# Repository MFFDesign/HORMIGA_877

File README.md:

# HORMIGA_877
Conjunto de procedimientos para, usar mas facilmente la placa Hormiga 877

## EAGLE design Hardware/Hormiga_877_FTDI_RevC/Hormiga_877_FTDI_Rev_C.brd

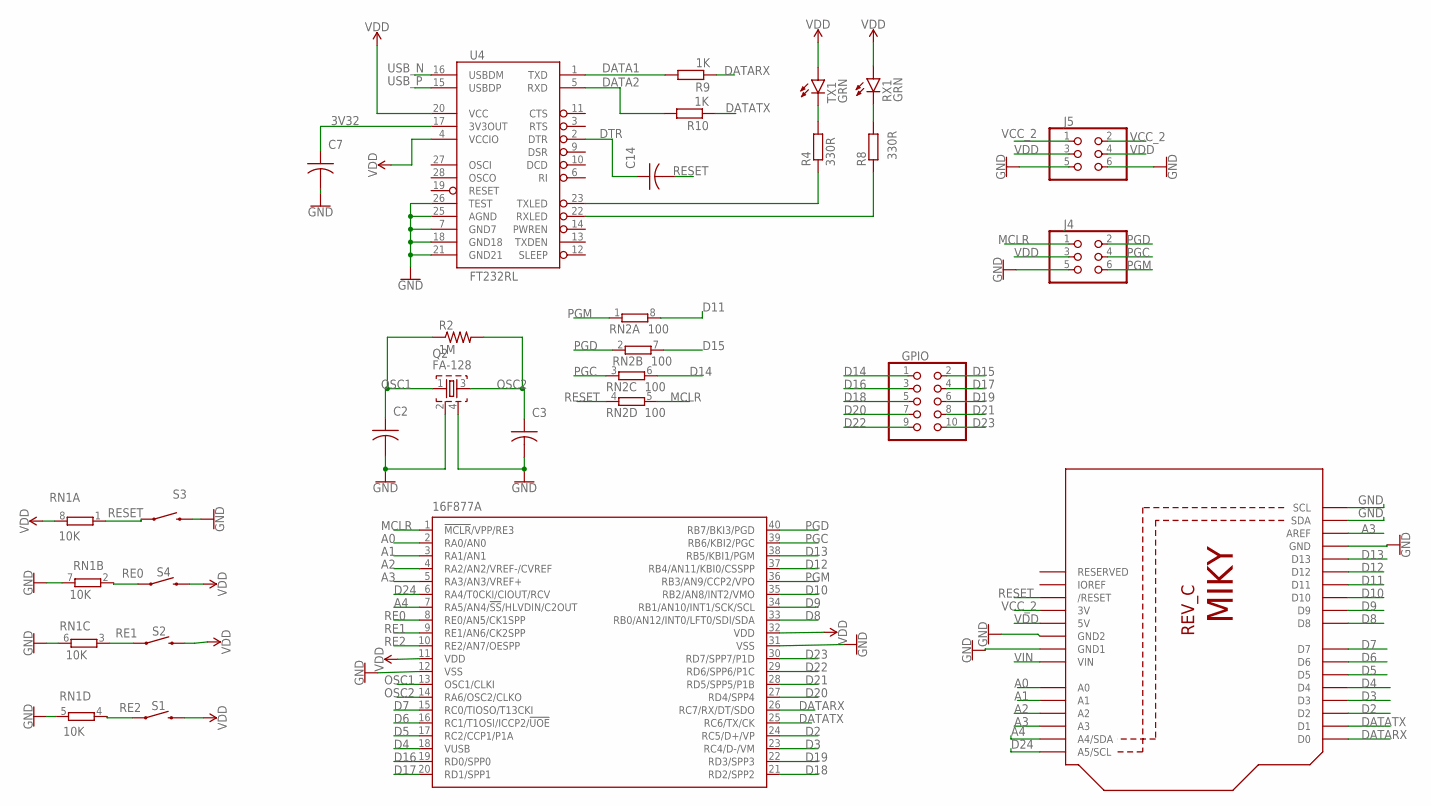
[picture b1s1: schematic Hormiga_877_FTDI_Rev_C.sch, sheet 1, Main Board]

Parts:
16F877A: PIC18F4550_40; DIL40
C2, C3: 15pF; C0603; MPN CC0402JRNPO9BN150
C7, C14: 0.1uF; C0603; MPN C0603C103J1RACTU
GPIO: PINHD-2X5; 2X05
J4: ICSP; 2X03
J5: POWER; 2X03
Q2: FA-128
R2: 1M; R0603
R4, R8: 330R; R0805; MPN ERJ-6GEYJ331V
R9, R10: 1K; R0805; MPN EXB-V8V103JV
RN1: 10K; 0603-ARC; MPN EXB-V8V103JV
RN2: 100; 0603-ARC
RX1: GRN; CHIP-LED0603; MPN HSME-C191
S1, S2, S3, S4: MOMENTARY-SWITCH-SPST-SMD-5.2-REDUNDANT; TACTILE_SWITCH_SMD_5.2MM; MPN TL3301AF160QG
TX1: GRN; CHIP-LED0603; MPN HSME-C191
U2: ARDUINOR3-DIMENSION; ARDUINOR3
U4: FT232RL; SSOP28DB; MPN FT232RL-REEL

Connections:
3V32: C7.1, U4.17 (3V3OUT)
A0: 16F877A.2 (RA0/AN0), U2.A0
A1: 16F877A.3 (RA1/AN1), U2.A1
A2: 16F877A.4 (RA2/AN2/VREF-/CVREF), U2.A2
A3: 16F877A.5 (RA3/AN3/VREF+), U2.A3, U2.AREF
A4: 16F877A.7 (RA5/AN4/!SS!/HLVDIN/C2OUT), U2.A4 (A4/SDA)
D2: 16F877A.24 (RC5/D+/VP), U2.D2
D3: 16F877A.23 (RC4/D-/VM), U2.D3
D4: 16F877A.18 (VUSB), U2.D4
D5: 16F877A.17 (RC2/CCP1/P1A), U2.D5
D6: 16F877A.16 (RC1/T1OSI/ICCP2/!UOE), U2.D6
D7: 16F877A.15 (RC0/TIOSO/T13CKI), U2.D7
D8: 16F877A.33 (RB0/AN12/INT0/LFT0/SDI/SDA), U2.D8
D9: 16F877A.34 (RB1/AN10/INT1/SCK/SCL), U2.D9
D10: 16F877A.35 (RB2/AN8/INT2/VMO), U2.D10
D11: RN2.8 (2), U2.D11
D12: 16F877A.37 (RB4/AN11/KBI0/CSSPP), U2.D12
D13: 16F877A.38 (RB5/KBI1/PGM), U2.D13; also elsewhere on the board
D14: GPIO.1, RN2.6 (2)
D15: GPIO.2, RN2.7 (2)
D16: 16F877A.19 (RD0/SPP0), GPIO.3
D17: 16F877A.20 (RD1/SPP1), GPIO.4
D18: 16F877A.21 (RD2/SPP2), GPIO.5
D19: 16F877A.22 (RD3/SPP3), GPIO.6
D20: 16F877A.27 (RD4/SPP4), GPIO.7
D21: 16F877A.28 (RD5/SPP5/P1B), GPIO.8
D22: 16F877A.29 (RD6/SPP6/P1C), GPIO.9
D23: 16F877A.30 (RD7/SPP7/P1D), GPIO.10
D24: 16F877A.6 (RA4/T0CKI/CIOUT/RCV), U2.A5 (A5/SCL)
DATA1: R9.2, U4.1 (TXD)
DATA2: R10.2, U4.5 (RXD)
DATARX: 16F877A.26 (RC7/RX/DT/SDO), R9.1, U2.D0
DATATX: 16F877A.25 (RC6/TX/CK), R10.1, U2.D1
DTR: C14.1, U4.2 (DTR)
GND: 16F877A.12 (VSS), 16F877A.31 (VSS), C2.2, C3.2, C7.2, J4.5, J5.5, J5.6, Q2.2, Q2.4, RN1.5 (2), RN1.6 (2), RN1.7 (2), S3.3 (2), S3.4 (2), U2.GND, U2.GND1, U2.GND2, U2.SCL, U2.SDA, U4.7 (GND7), U4.18 (GND18), U4.21 (GND21), U4.25 (AGND), U4.26 (TEST); also elsewhere on the board
MCLR: 16F877A.1 (!MCLR!/VPP/RE3), J4.1, RN2.5 (2)
OSC1: 16F877A.13 (OSC1/CLKI), C2.1, Q2.1, R2.1
OSC2: 16F877A.14 (RA6/OSC2/CLKO), C3.1, Q2.3, R2.2
PGC: 16F877A.39 (RB6/KBI2/PGC), J4.4, RN2.3 (1)
PGD: 16F877A.40 (RB7/BKI3/PGD), J4.2, RN2.2 (1)
PGM: 16F877A.36 (RB3/AN9/CCP2/VPO), J4.6, RN2.1
RE0: 16F877A.8 (RE0/AN5/CK1SPP), RN1.2 (1), S4.1, S4.2 (1)
RE1: 16F877A.9 (RE1/AN6/CK2SPP), RN1.3 (1), S2.1, S2.2 (1)
RE2: 16F877A.10 (RE2/AN7/OESPP), RN1.4 (1), S1.1, S1.2 (1)
RESET: C14.2, RN1.1, RN2.4 (1), S3.1, S3.2 (1), U2.RESET (/RESET)
RX1: R8.2, RX1.C
RXLED: R8.1, U4.22 (RXLED)
TX1: R4.2, TX1.C
TXLED: R4.1, U4.23 (TXLED)
USB_N: U4.16 (USBDM); also elsewhere on the board
USB_P: U4.15 (USBDP); also elsewhere on the board
VCC_2: J5.1, J5.2, U2.3V; also elsewhere on the board
VDD: 16F877A.11 (VDD), 16F877A.32 (VDD), J4.3, J5.3, J5.4, RN1.8 (2), RX1.A, S1.3 (2), S1.4 (2), S2.3 (2), S2.4 (2), S4.3 (2), S4.4 (2), TX1.A, U2.5V, U4.4 (VCCIO), U4.20 (VCC); also elsewhere on the board
VIN: U2.VIN; also elsewhere on the board

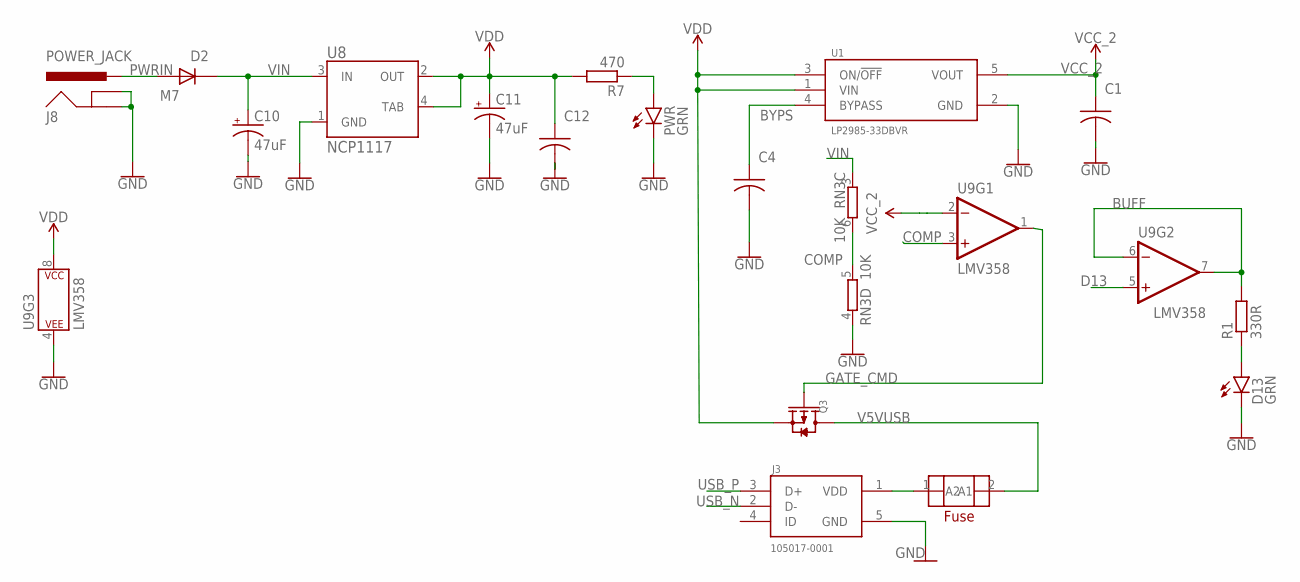
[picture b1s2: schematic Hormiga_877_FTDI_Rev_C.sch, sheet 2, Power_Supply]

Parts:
C1: 1.0uF; C0603; MPN C1608X5R1E105K080AC
C4: 10nF; C0603; MPN C0603C103K1RACTU
C10, C11: 47uF; PANASONIC_D; MPN EEE-1CA470WR
C12: 0.1uF; C0603; MPN C0603C103J1RACTU
D2: M7; DIOM505270X240; MPN RFN1LAM7STFTR
D13: GRN; CHIP-LED0603; MPN HSME-C191
FUSE: FUSE0603; R0603
J3: 105017-0001; MOLEX_105017-0001
J8: POWER_JACK; POWER_JACK_PTH; MPN FC681465P
PWR: GRN; CHIP-LED0603; MPN HSME-C191
Q3: SMD-MOSFET-P-CH-20V-2A(SOT-23); SOT-23; MPN FDN340P
R1: 330R; R0805; MPN ERJ-6GEYJ331V
R7: 470; R0805; MPN ERJ-6GEYJ471V
RN3: 10K; 0603-ARC; MPN EXB-V8V103JV
U1: LP2985-33DBVR; SOT95P280X145-5N; MPN LP2985-33DBVR
U8: NCP1117; SOT223; MPN NCP1117ST50T3G
U9: LMV358; SO08; MPN LMV358AM8X

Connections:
BUFF: R1.2, U9.6 (-IN), U9.7 (OUT)
BYPS: C4.1, U1.4 (BYPASS)
COMP: RN3.5 (2), RN3.6 (2), U9.3 (+IN)
D13: U9.5 (+IN); also elsewhere on the board
D13LED: D13.A, R1.1
GATE_CMD: Q3.1 (G), U9.1 (OUT)
GND: C1.2, C4.2, C10.-, C11.-, C12.2, D13.C, J3.5 (GND), J8.GND, J8.GNDBREAK, PWR.C, RN3.4 (1), U1.2 (GND), U8.1 (GND), U9.4 (P$V-); also elsewhere on the board
PWRIN: D2.A, J8.PWR
PWRLED: PWR.A, R7.1
USB_N: J3.2 (D-); also elsewhere on the board
USB_P: J3.3 (D+); also elsewhere on the board
V5VUSB: FUSE.2 (A2), Q3.3 (D)
VCC_2: C1.1, U1.5 (VOUT), U9.2 (-IN); also elsewhere on the board
VDD: C11.+, C12.1, Q3.2 (S), R7.2, U1.1 (VIN), U1.3 (ON/!OFF), U8.2 (OUT), U8.4 (TAB), U9.8 (P$V+); also elsewhere on the board
VDD5: FUSE.1 (A1), J3.1 (VDD)
VIN: C10.+, D2.C, RN3.3 (1), U8.3 (IN); also elsewhere on the board

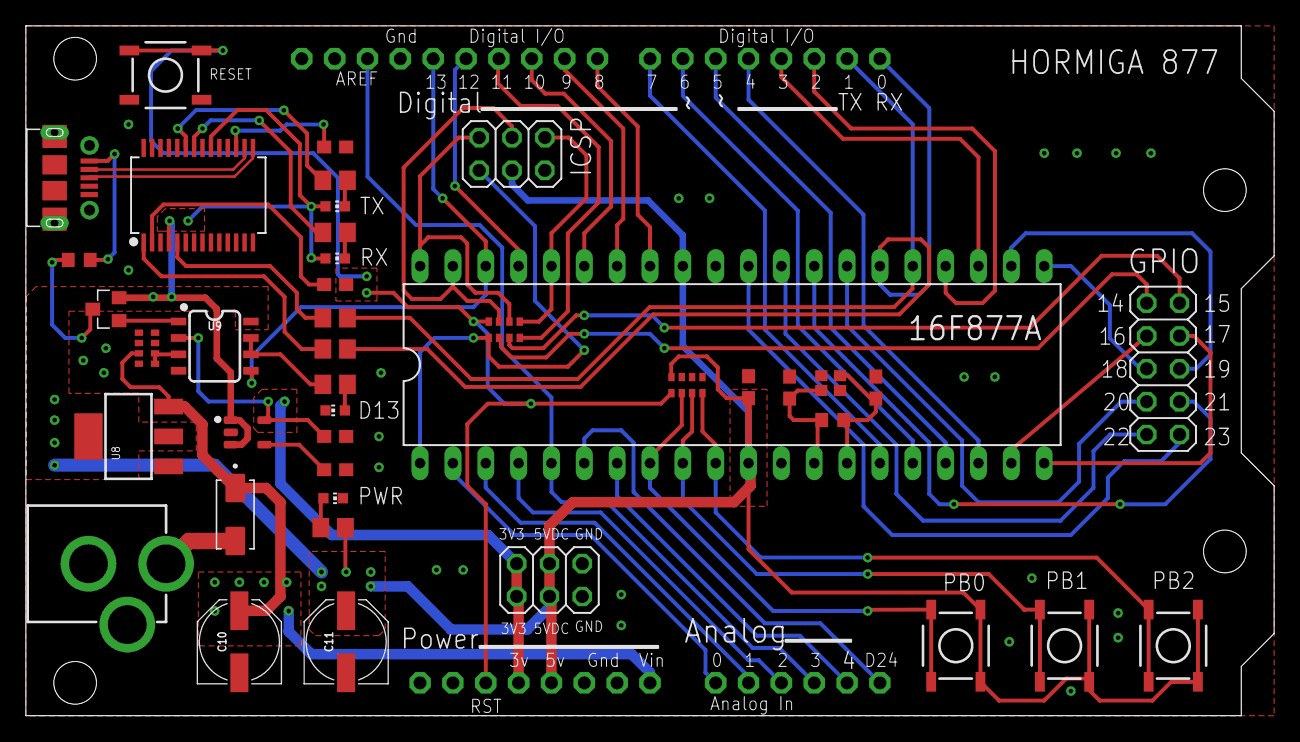
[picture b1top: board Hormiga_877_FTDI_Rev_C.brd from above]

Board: 2 copper layers, 96.5 x 53.3 mm, 42 parts (0 on the bottom side), 63 nets.

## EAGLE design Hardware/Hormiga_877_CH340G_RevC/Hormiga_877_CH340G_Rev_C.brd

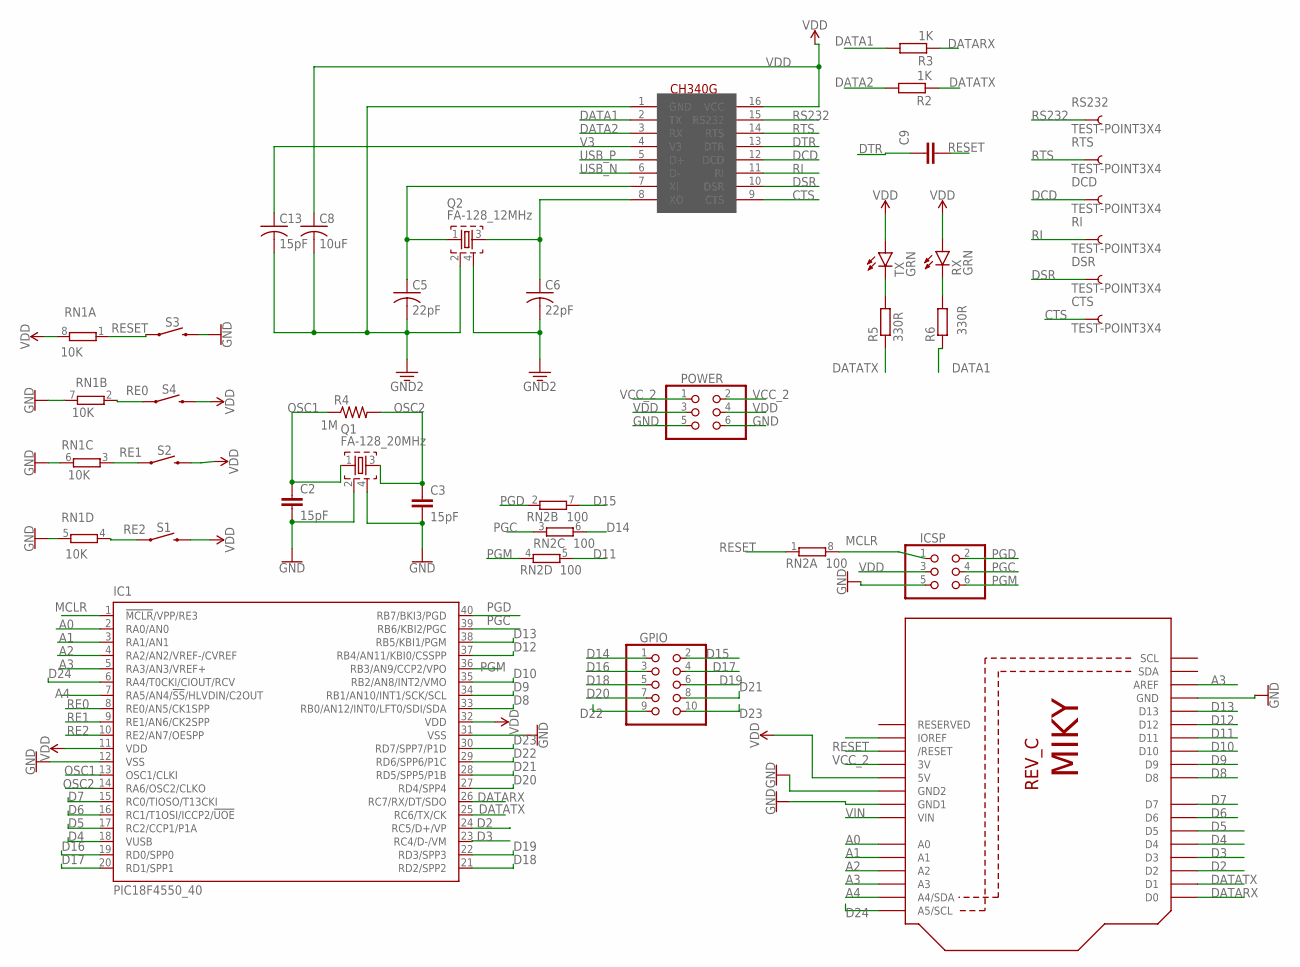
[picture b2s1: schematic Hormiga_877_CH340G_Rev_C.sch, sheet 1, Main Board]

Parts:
C2, C3: 15pF; 0402; MPN CC0402JRNPO9BN150
C5, C6: 22pF; C0603
C8: 10uF; C0603
C9: 0.1uF; C0603; MPN C0603C103J1RACTU
C13: 15pF; C0603
CTS: TEST-POINT3X4; PAD.03X.04
DCD: TEST-POINT3X4; PAD.03X.04
DSR: TEST-POINT3X4; PAD.03X.04
GPIO: PINHD-2X5; 2X05
IC1: PIC18F4550_40; DIL40
ICSP: icsp; 2X03
POWER: POWER; 2X03
Q1: FA-128_20MHz; FA-128
Q2: FA-128_12MHz; FA-128
R2, R3: 1K; R0805; MPN EXB-V8V103JV
R4: 1M; R0603
R5, R6: 330R; R0805; MPN ERJ-6GEYJ331V
RI: TEST-POINT3X4; PAD.03X.04
RN1: 10K; 0603-ARC; MPN EXB-V8V103JV
RN2: 100; 0603-ARC
RS232: TEST-POINT3X4; PAD.03X.04
RTS: TEST-POINT3X4; PAD.03X.04
RX: GRN; CHIP-LED0603; MPN HSME-C191
S1, S2, S3, S4: MOMENTARY-SWITCH-SPST-SMD-5.2-REDUNDANT; TACTILE_SWITCH_SMD_5.2MM; MPN TL3301AF160QG
TX: GRN; CHIP-LED0603; MPN HSME-C191
U2: ARDUINOR3-DIMENSION; ARDUINOR3
U$1: CH340G; SOIC16

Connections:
A0: IC1.2 (RA0/AN0), U2.A0
A1: IC1.3 (RA1/AN1), U2.A1
A2: IC1.4 (RA2/AN2/VREF-/CVREF), U2.A2
A3: IC1.5 (RA3/AN3/VREF+), U2.A3, U2.AREF
A4: IC1.7 (RA5/AN4/!SS!/HLVDIN/C2OUT), U2.A4 (A4/SDA)
CTS: CTS.P$1, U$1.9 (CTS)
D2: IC1.24 (RC5/D+/VP), U2.D2
D3: IC1.23 (RC4/D-/VM), U2.D3
D4: IC1.18 (VUSB), U2.D4
D5: IC1.17 (RC2/CCP1/P1A), U2.D5
D6: IC1.16 (RC1/T1OSI/ICCP2/!UOE), U2.D6
D7: IC1.15 (RC0/TIOSO/T13CKI), U2.D7
D8: IC1.33 (RB0/AN12/INT0/LFT0/SDI/SDA), U2.D8
D9: IC1.34 (RB1/AN10/INT1/SCK/SCL), U2.D9
D10: IC1.35 (RB2/AN8/INT2/VMO), U2.D10
D11: RN2.5 (2), U2.D11
D12: IC1.37 (RB4/AN11/KBI0/CSSPP), U2.D12
D13: IC1.38 (RB5/KBI1/PGM), U2.D13; also elsewhere on the board
D14: GPIO.1, RN2.6 (2)
D15: GPIO.2, RN2.7 (2)
D16: GPIO.3, IC1.19 (RD0/SPP0)
D17: GPIO.4, IC1.20 (RD1/SPP1)
D18: GPIO.5, IC1.21 (RD2/SPP2)
D19: GPIO.6, IC1.22 (RD3/SPP3)
D20: GPIO.7, IC1.27 (RD4/SPP4)
D21: GPIO.8, IC1.28 (RD5/SPP5/P1B)
D22: GPIO.9, IC1.29 (RD6/SPP6/P1C)
D23: GPIO.10, IC1.30 (RD7/SPP7/P1D)
D24: IC1.6 (RA4/T0CKI/CIOUT/RCV), U2.A5 (A5/SCL)
DATA1: R3.2, R6.1, U$1.2 (TX)
DATA2: R2.2, U$1.3 (RX)
DATARX: IC1.26 (RC7/RX/DT/SDO), R3.1, U2.D0
DATATX: IC1.25 (RC6/TX/CK), R2.1, R5.1, U2.D1
DCD: DCD.P$1, U$1.12 (DCD)
DSR: DSR.P$1, U$1.10 (DSR)
DTR: C9.1, U$1.13 (DTR)
GND: C2.2, C3.2, C5.2, C6.2, C8.2, C13.2, IC1.12 (VSS), IC1.31 (VSS), ICSP.5, POWER.5, POWER.6, Q1.2, Q1.4, Q2.2, Q2.4, RN1.5 (2), RN1.6 (2), RN1.7 (2), S3.3 (2), S3.4 (2), U2.GND, U2.GND1, U2.GND2, U$1.1 (GND); also elsewhere on the board
LEDRX: R6.2, RX.C
LEDTX: R5.2, TX.C
MCLR: IC1.1 (!MCLR!/VPP/RE3), ICSP.1, RN2.8 (2)
OSC1: C2.1, IC1.13 (OSC1/CLKI), Q1.1, R4.1
OSC2: C3.1, IC1.14 (RA6/OSC2/CLKO), Q1.3, R4.2
PGC: IC1.39 (RB6/KBI2/PGC), ICSP.4, RN2.3 (1)
PGD: IC1.40 (RB7/BKI3/PGD), ICSP.2, RN2.2 (1)
PGM: IC1.36 (RB3/AN9/CCP2/VPO), ICSP.6, RN2.4 (1)
RE0: IC1.8 (RE0/AN5/CK1SPP), RN1.2 (1), S4.1, S4.2 (1)
RE1: IC1.9 (RE1/AN6/CK2SPP), RN1.3 (1), S2.1, S2.2 (1)
RE2: IC1.10 (RE2/AN7/OESPP), RN1.4 (1), S1.1, S1.2 (1)
RESET: C9.2, RN1.1, RN2.1, S3.1, S3.2 (1), U2.RESET (/RESET)
RI: RI.P$1, U$1.11 (RI)
RS232: RS232.P$1, U$1.15 (RS232)
RTS: RTS.P$1, U$1.14 (RTS)
USB_N: U$1.6 (D-); also elsewhere on the board
USB_P: U$1.5 (D+); also elsewhere on the board
V3: C13.1, U$1.4 (V3)
VCC_2: POWER.1, POWER.2, U2.3V; also elsewhere on the board
VDD: C8.1, IC1.11 (VDD), IC1.32 (VDD), ICSP.3, POWER.3, POWER.4, RN1.8 (2), RX.A, S1.3 (2), S1.4 (2), S2.3 (2), S2.4 (2), S4.3 (2), S4.4 (2), TX.A, U2.5V, U$1.16 (VCC); also elsewhere on the board
VIN: U2.VIN; also elsewhere on the board
XI: C5.1, Q2.1, U$1.7 (XI)
XO: C6.1, Q2.3, U$1.8 (XO)

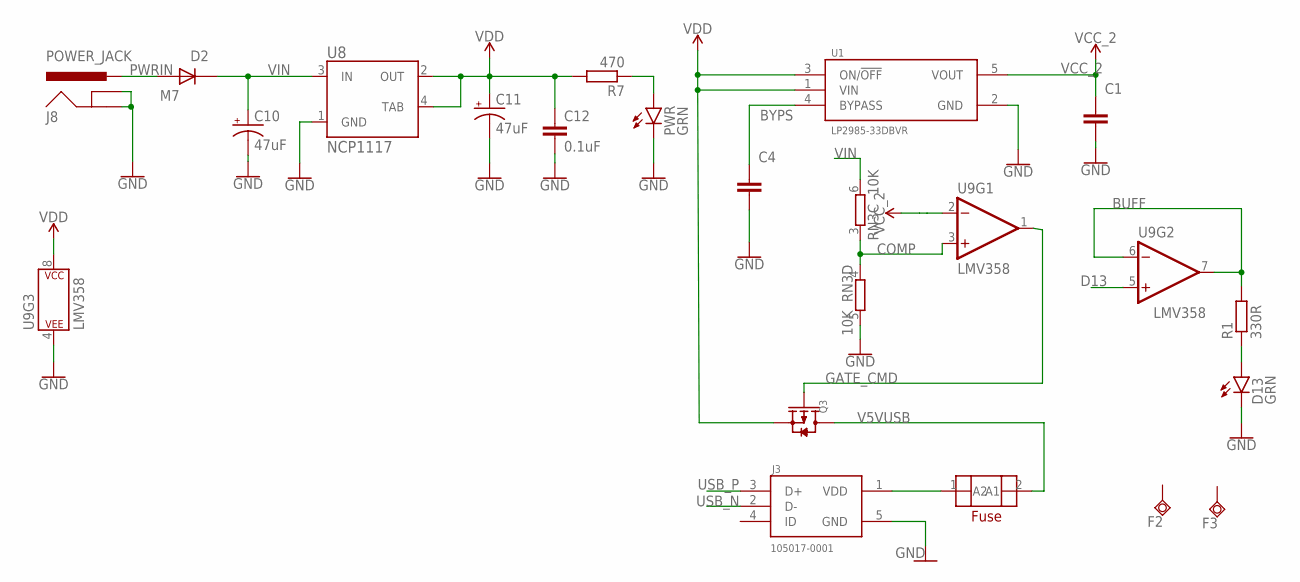
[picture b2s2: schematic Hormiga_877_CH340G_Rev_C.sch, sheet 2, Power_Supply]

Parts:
C1: 1.0uF; C0603; MPN C1608X5R1E105K080AC
C4: 10nF; C0603; MPN C0603C103K1RACTU
C10, C11: 47uF; PANASONIC_D; MPN EEE-1CA470WR
C12: 0.1uF; 0402; MPN C0603C103J1RACTU
D2: M7; DIOM505270X240; MPN RFN1LAM7STFTR
D13: GRN; CHIP-LED0603; MPN HSME-C191
F2, F3: TPSQTP10R; TP10R
FUSE: FUSE0603; R0603
J3: 105017-0001; MOLEX_105017-0001
J8: POWER_JACK; POWER_JACK_PTH; MPN FC681465P
PWR: GRN; CHIP-LED0603; MPN HSME-C191
Q3: SMD-MOSFET-P-CH-20V-2A(SOT-23); SOT-23; MPN FDN340P
R1: 330R; R0805; MPN ERJ-6GEYJ331V
R7: 470; R0805; MPN ERJ-6GEYJ471V
RN3: 10K; 0603-ARC; MPN EXB-V8V103JV
U1: LP2985-33DBVR; SOT95P280X145-5N; MPN LP2985-33DBVR
U8: NCP1117; SOT223; MPN NCP1117ST50T3G
U9: LMV358; SO08; MPN LMV358AM8X

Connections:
BUFF: R1.2, U9.6 (-IN), U9.7 (OUT)
BYPS: C4.1, U1.4 (BYPASS)
COMP: RN3.3 (1), RN3.4 (1), U9.3 (+IN)
D13: U9.5 (+IN); also elsewhere on the board
D13LED: D13.A, R1.1
FUSE: FUSE.1 (A1), J3.1 (VDD)
GATE_CMD: Q3.1 (G), U9.1 (OUT)
GND: C1.2, C4.2, C10.-, C11.-, C12.2, D13.C, J3.5 (GND), J8.GND, J8.GNDBREAK, PWR.C, RN3.5 (2), U1.2 (GND), U8.1 (GND), U9.4 (P$V-); also elsewhere on the board
ONLED: PWR.A, R7.1
PWRIN: D2.A, J8.PWR
USB_N: J3.2 (D-); also elsewhere on the board
USB_P: J3.3 (D+); also elsewhere on the board
V5VUSB: FUSE.2 (A2), Q3.3 (D)
VCC_2: C1.1, U1.5 (VOUT), U9.2 (-IN); also elsewhere on the board
VDD: C11.+, C12.1, Q3.2 (S), R7.2, U1.1 (VIN), U1.3 (ON/!OFF), U8.2 (OUT), U8.4 (TAB), U9.8 (P$V+); also elsewhere on the board
VIN: C10.+, D2.C, RN3.6 (2), U8.3 (IN); also elsewhere on the board

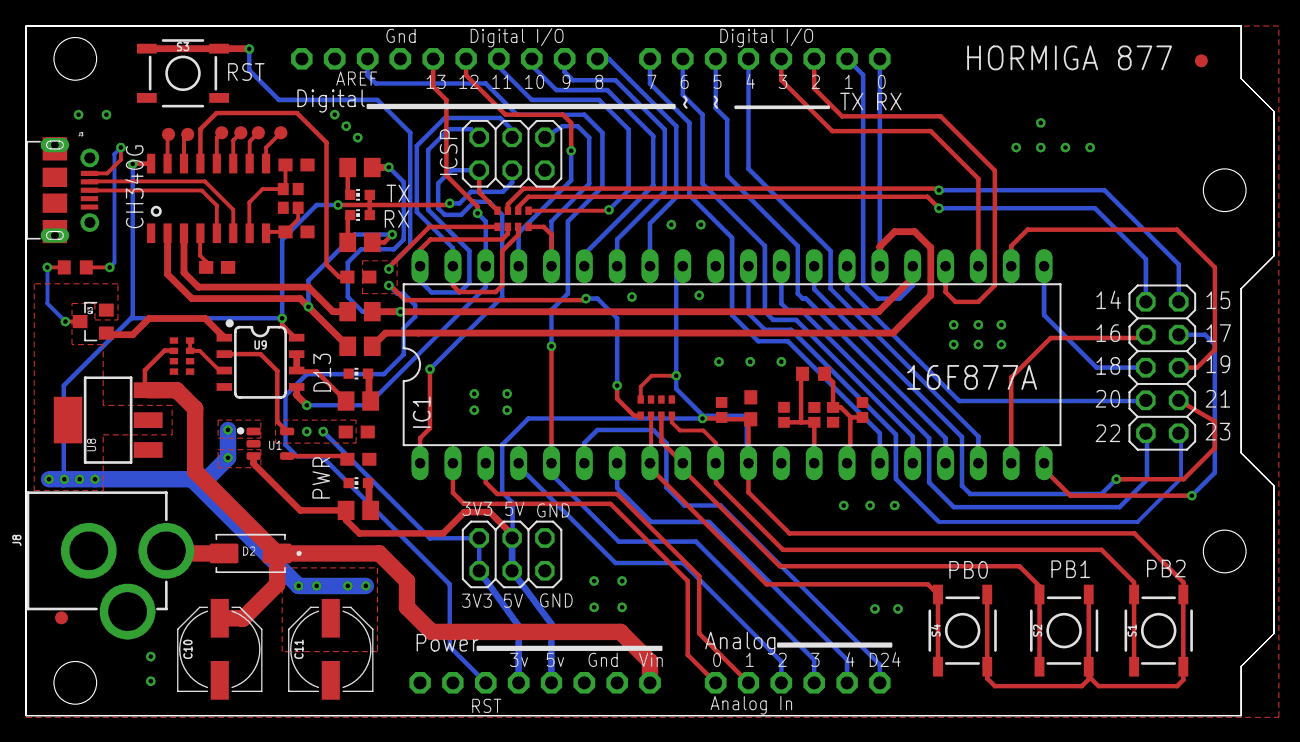
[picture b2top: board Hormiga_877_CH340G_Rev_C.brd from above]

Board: 2 copper layers, 96.5 x 53.3 mm, 54 parts (0 on the bottom side), 69 nets.

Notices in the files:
parts and their libraries:
SparkFun-Capacitors: Licensing: Creative Commons ShareAlike 4.0 International - https://creativecommons.org/licenses/by-sa/4.0
